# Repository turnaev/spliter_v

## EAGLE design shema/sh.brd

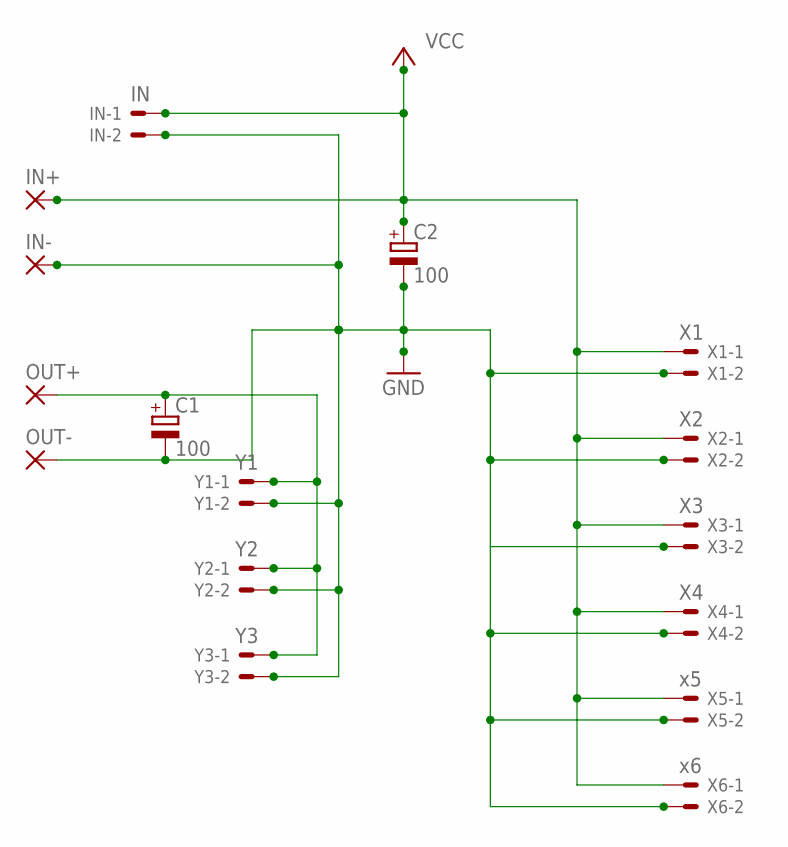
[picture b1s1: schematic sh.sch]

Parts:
C1, C2: 100; E5-10,5
IN: IN; 70543-02
IN+: 3,17/1,3
IN-: 3,17/1,3
OUT+: 3,17/1,3
OUT-: 3,17/1,3
X1: X1; 70543-02
X2: X2; 70543-02
X3: X3; 70543-02
X4: X4; 70543-02
X5: x5; 70543-02
X6: x6; 70543-02
Y1: Y1; 70543-02
Y2: Y2; 70543-02
Y3: Y3; 70543-02

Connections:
GND: C1.-, C2.-, IN.2, IN-.1, OUT-.1, X1.2, X2.2, X3.2, X4.2, X5.2, X6.2, Y1.2, Y2.2, Y3.2
unnamed: C1.+, OUT+.1, Y1.1, Y2.1, Y3.1
VCC: C2.+, IN.1, IN+.1, X1.1, X2.1, X3.1, X4.1, X5.1, X6.1

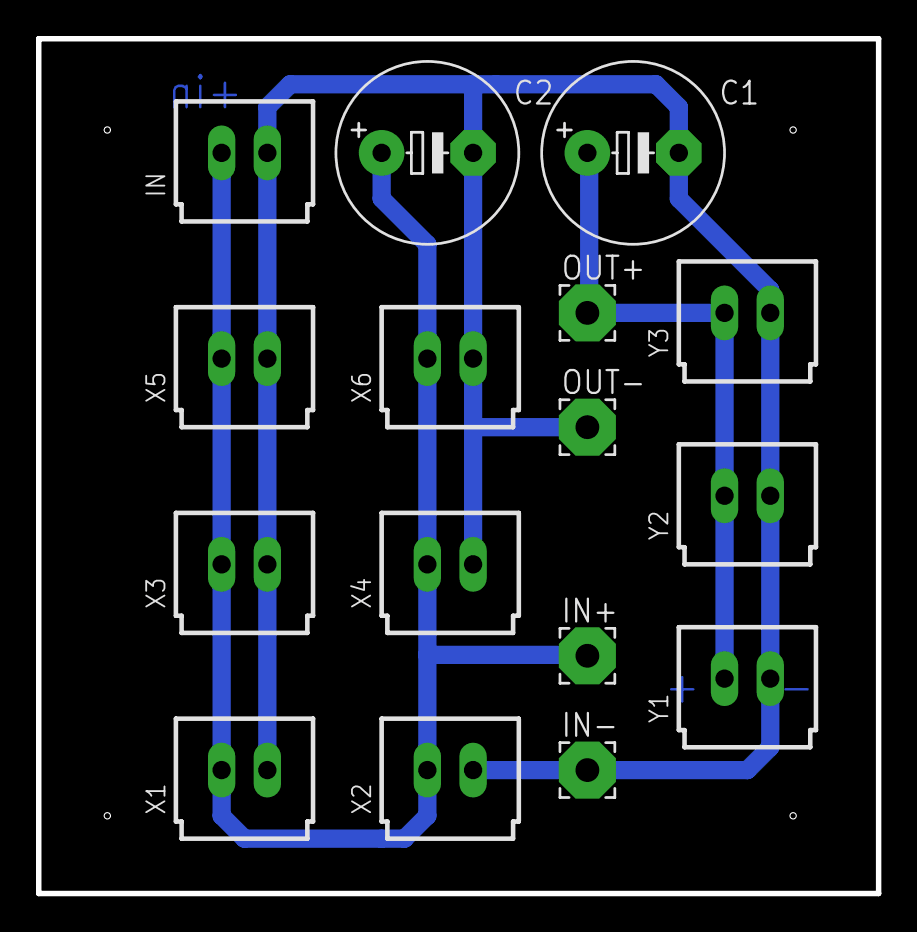
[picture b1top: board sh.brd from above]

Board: 2 copper layers, 46.7 x 47.5 mm, 16 parts (0 on the bottom side), 3 nets.

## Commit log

2020-02-14 shema
